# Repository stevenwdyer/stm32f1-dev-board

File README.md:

# stm32f1-dev-board

This board is an STM32F103-based development platform, designed for prototyping and developing embedded applications. The design includes:

* An STM32F103C8T6 microcontroller, which features an ARM Cortex-M3 core and 128kB of flash.

* Support for multiple communication protocols, including CANbus, LINbus, I<sup>2</sup>C, SPI, USB, and UART.

* Dual clock sources, featuring a 32.768kHz crystal for precise RTC functionality, as well as an 8MHz system clock.

* An SWD interface, enabling firmware flashing and in-circuit debugging using an external ST-LINK.

* A 5V to 3.3V linear regulator, providing power for the MCU and all onboard circuitry from the USB input.

* User interface, via a reset button and a power indicator LED.

* A standardized form factor, with a 19x50mm footprint and 2.54mm pitch headers, enabling compatibility with standard breadboards for rapid prototyping.

### Images ###

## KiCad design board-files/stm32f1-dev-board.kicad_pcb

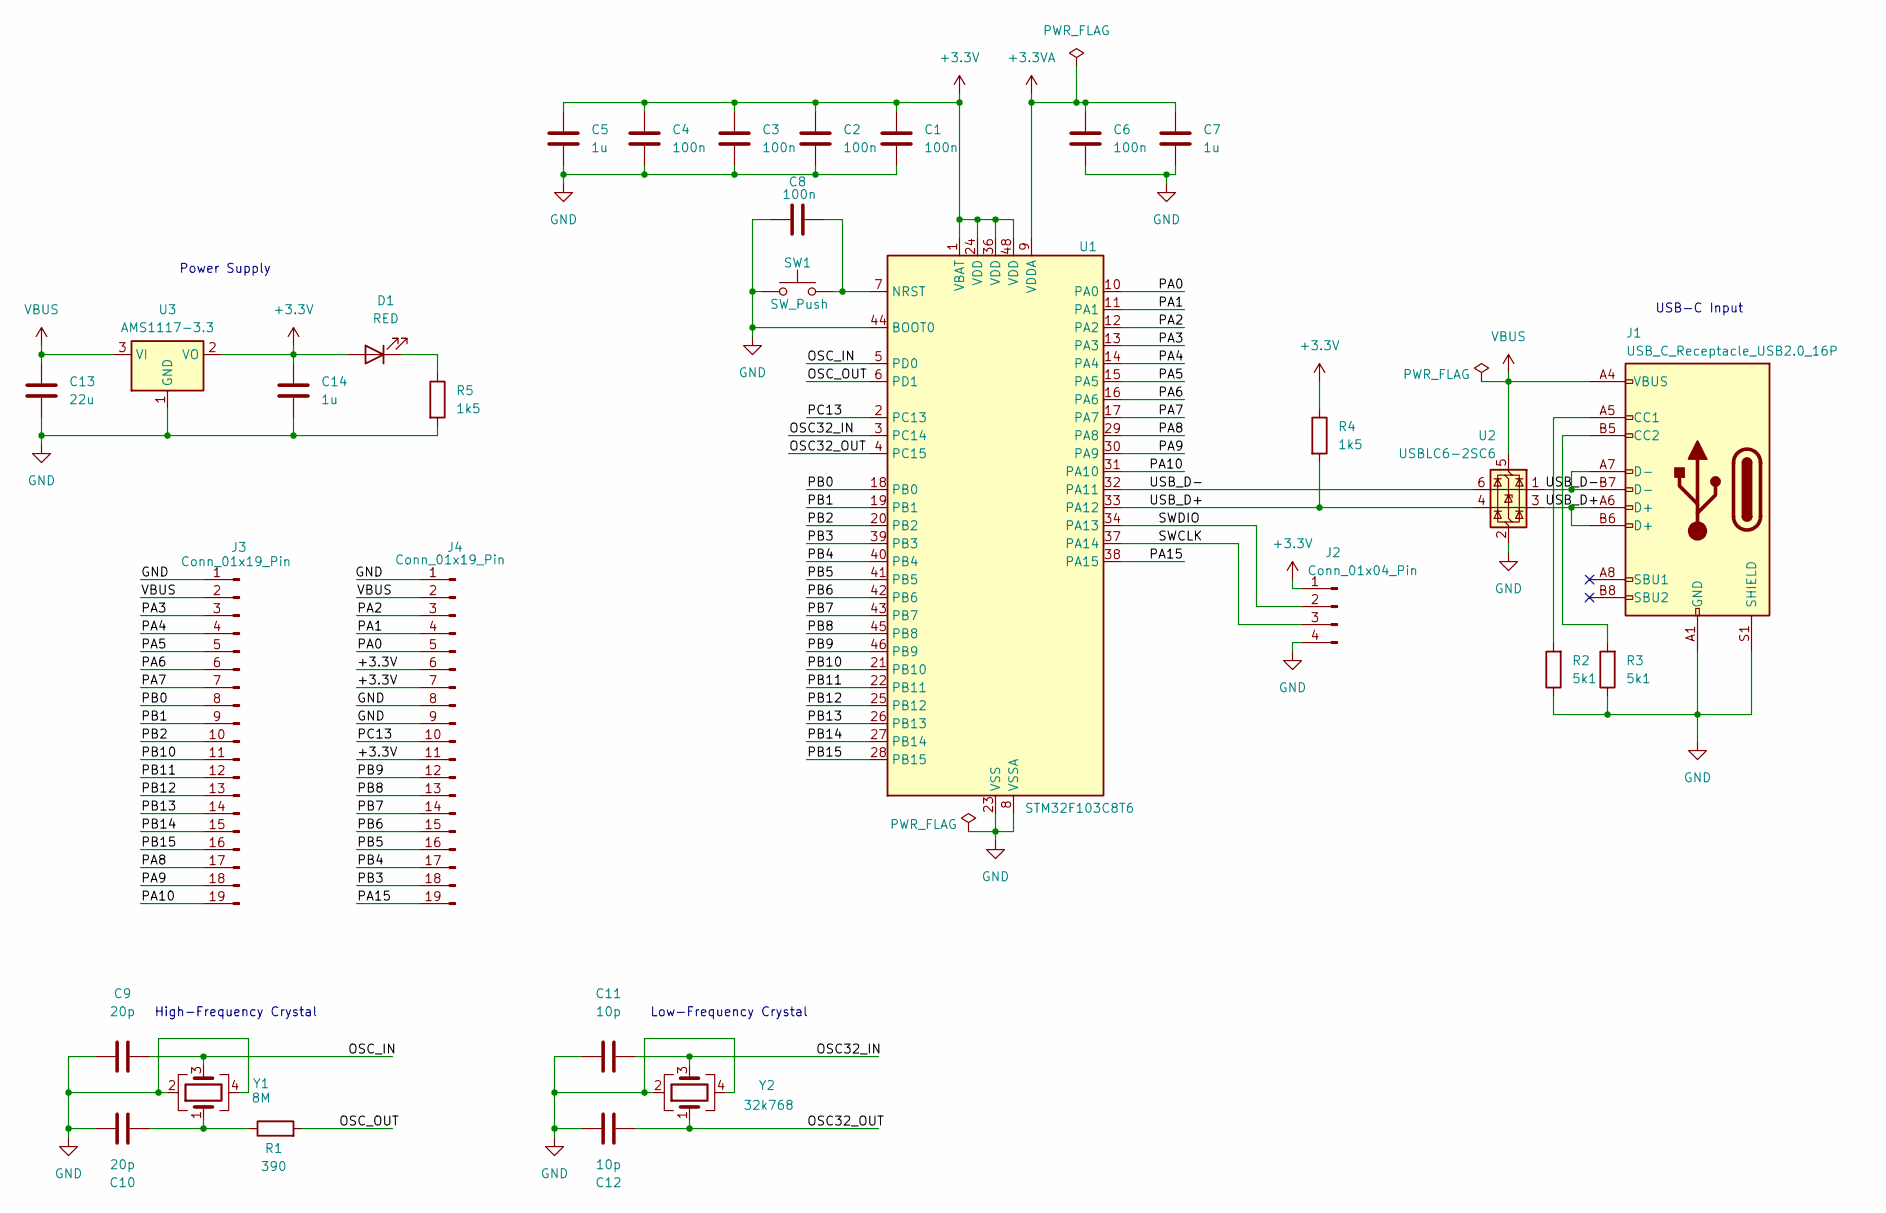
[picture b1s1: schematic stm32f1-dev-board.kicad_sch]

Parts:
C1, C2, C3, C4, C6, C8: 100n; C_0402_1005Metric
C5, C7, C14: 1u; C_0402_1005Metric
C9, C10: 20p; C_0402_1005Metric
C11, C12: 10p; C_0402_1005Metric
C13: 22u; C_0805_2012Metric
D1: RED; LED_0201_0603Metric
J1: USB_C_Receptacle_USB2.0_16P; USB_C_Receptacle_GCT_USB4105-xx-A_16P_TopMnt_Horizontal
J2: Conn_01x04_Pin; PinHeader_1x04_P2.54mm_Vertical
J3, J4: Conn_01x19_Pin; PinHeader_1x19_P2.54mm_Vertical
R1: 390; R_0402_1005Metric
R2, R3: 5k1; R_0402_1005Metric
R4, R5: 1k5; R_0402_1005Metric
SW1: SW_Push; SW_SPST_PTS810
U1: STM32F103C8T6; LQFP-48_7x7mm_P0.5mm
U2: USBLC6-2SC6; SOT-23-6
U3: AMS1117-3.3; SOT-223-3_TabPin2
Y1: 8M; Crystal_SMD_3225-4Pin_3.2x2.5mm
Y2: 32k768; Crystal_SMD_3225-4Pin_3.2x2.5mm

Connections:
+3.3V: C1.1, C2.1, C3.1, C4.1, C5.1, C14.1, D1.2 (A), J2.1, J4.6, J4.7, J4.11, R4.1, U1.1 (VBAT), U1.24 (VDD), U1.36 (VDD), U1.48 (VDD), U3.2 (VO)
+3.3VA: C6.1, C7.1, U1.9 (VDDA)
/OSC32_IN: C11.2, U1.3 (PC14), Y2.3
/OSC32_OUT: C12.2, U1.4 (PC15), Y2.1
/OSC_IN: C9.2, U1.5 (PD0), Y1.3
/OSC_OUT: R1.2, U1.6 (PD1)
/PA0: J4.5, U1.10 (PA0)
/PA1: J4.4, U1.11 (PA1)
/PA2: J4.3, U1.12 (PA2)
/PA3: J3.3, U1.13 (PA3)
/PA4: J3.4, U1.14 (PA4)
/PA5: J3.5, U1.15 (PA5)
/PA6: J3.6, U1.16 (PA6)
/PA7: J3.7, U1.17 (PA7)
/PA8: J3.17, U1.29 (PA8)
/PA9: J3.18, U1.30 (PA9)
/PA10: J3.19, U1.31 (PA10)
/PA15: J4.19, U1.38 (PA15)
/PB0: J3.8, U1.18 (PB0)
/PB1: J3.9, U1.19 (PB1)
/PB2: J3.10, U1.20 (PB2)
/PB3: J4.18, U1.39 (PB3)
/PB4: J4.17, U1.40 (PB4)
/PB5: J4.16, U1.41 (PB5)
/PB6: J4.15, U1.42 (PB6)
/PB7: J4.14, U1.43 (PB7)
/PB8: J4.13, U1.45 (PB8)
/PB9: J4.12, U1.46 (PB9)
/PB10: J3.11, U1.21 (PB10)
/PB11: J3.12, U1.22 (PB11)
/PB12: J3.13, U1.25 (PB12)
/PB13: J3.14, U1.26 (PB13)
/PB14: J3.15, U1.27 (PB14)
/PB15: J3.16, U1.28 (PB15)
/PC13: J4.10, U1.2 (PC13)
/SWCLK: J2.3, U1.37 (PA14)
/SWDIO: J2.2, U1.34 (PA13)
/USB_D+: J1.A6 (D+), J1.B6 (D+), R4.2, U1.33 (PA12), U2.3 (I/O2), U2.4 (I/O2)
/USB_D-: J1.A7 (D-), J1.B7 (D-), U1.32 (PA11), U2.1 (I/O1), U2.6 (I/O1)
GND: C1.2, C2.2, C3.2, C4.2, C5.2, C6.2, C7.2, C8.1, C9.1, C10.1, C11.1, C12.1, C13.2, C14.2, J1.A1 (GND), J1.A12 (GND), J1.B1 (GND), J1.B12 (GND), J1.S1 (SHIELD), J2.4, J3.1, J4.1, J4.8, J4.9, R2.1, R3.1, R5.2, SW1.1, U1.8 (VSSA), U1.23 (VSS), U1.35 (VSS), U1.44 (BOOT0), U1.47 (VSS), U2.2 (GND), U3.1 (GND), Y1.2, Y1.4, Y2.2, Y2.4
unnamed: C10.2, R1.1, Y1.1
unnamed: D1.1 (K), R5.1
unnamed: J1.A5 (CC1), R2.2
unnamed: J1.B5 (CC2), R3.2
unnamed: C8.2, SW1.2, U1.7 (NRST)
VBUS: C13.1, J1.A4 (VBUS), J1.A9 (VBUS), J1.B4 (VBUS), J1.B9 (VBUS), J3.2, J4.2, U2.5 (VBUS), U3.3 (VI)

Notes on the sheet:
USB-C Input
Power Supply
High-Frequency Crystal
Low-Frequency Crystal

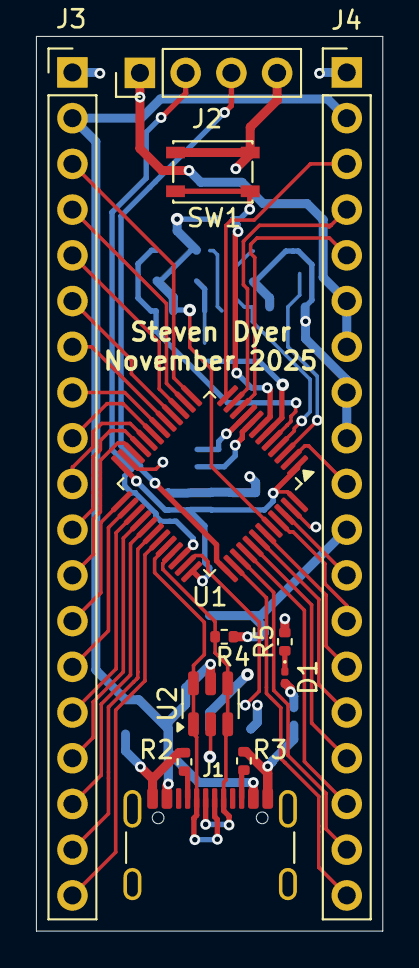
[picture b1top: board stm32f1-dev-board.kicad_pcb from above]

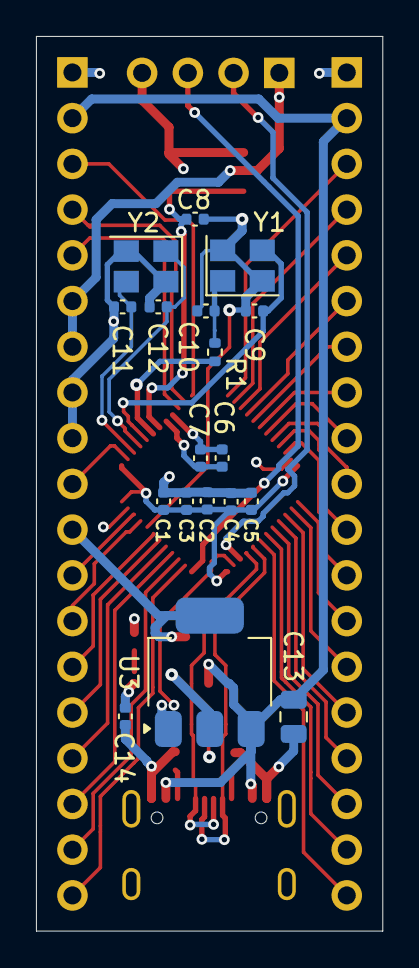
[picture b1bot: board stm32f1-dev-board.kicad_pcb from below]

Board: 4 copper layers, 19.2 x 49.7 mm, 30 parts (18 on the bottom side), 46 nets.

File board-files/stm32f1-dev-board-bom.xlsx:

Comment | Designator | Footprint | JLCPCB Part #（optional）
100n | C1,C2,C3,C4,C6,C8 | Capacitor_SMD:C_0402_1005Metric | https://mm.digikey.com/Volume0/opasdata/d220001/medias/docus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
1u | C5,C7,C14 | Capacitor_SMD:C_0402_1005Metric | https://mm.digikey.com/Volume0/opasdata/d220001/medias/docus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
20p | C9,C10 | Capacitor_SMD:C_0402_1005Metric | https://search.murata.co.jp/Ceramy/image/img/A01X/G101/ENG/G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
10p | C11,C12 | Capacitor_SMD:C_0402_1005Metric | https://mm.digikey.com/Volume0/opasdata/d220001/medias/docus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
22u | C13 | Capacitor_SMD:C_0805_2012Metric | https://mm.digikey.com/Volume0/opasdata/d220001/medias/docus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
RED | D1 | LED_SMD:LED_0201_0603Metric | https://www.we-online.com/components/products/datasheet/1540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
USB_C_Receptacle_USB2.0_16P | J1 | Connector_USB:USB_C_Receptacle_GCT_USB4105-xx-A_16P_TopMnt_Horizontal | https://www.usb.org/sites/default/files/documents/usb_type-c.zip
Conn_01x04_Pin | J2 | Connector_PinHeader_2.54mm:PinHeader_1x04_P2.54mm_Vertical | https://www.we-online.com/components/products/datasheet/6130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
Conn_01x19_Pin | J3,J4 | Connector_PinHeader_2.54mm:PinHeader_1x19_P2.54mm_Vertical | https://app.adam-tech.com/products/download/data_sheet/20160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
390 | R1 | Resistor_SMD:R_0402_1005Metric | https://www.yageo.com/upload/media/product/products/datashee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
5k1 | R2,R3 | Resistor_SMD:R_0402_1005Metric | https://www.digikey.ca/en/products/detail/yageo/RC0402FR-075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
1k5 | R4,R5 | Resistor_SMD:R_0402_1005Metric | https://www.yageo.com/upload/media/product/products/datashee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
SW_Push | SW1 | Button_Switch_SMD:SW_SPST_PTS810 | https://www.ckswitches.com/media/1476/pts810.pdf
STM32F103C8T6 | U1 | Package_QFP:LQFP-48_7x7mm_P0.5mm | https://www.st.com/resource/en/datasheet/stm32f103c8.pdf
USBLC6-2SC6 | U2 | Package_TO_SOT_SMD:SOT-23-6 | https://www.st.com/resource/en/datasheet/usblc6-2.pdf
AMS1117-3.3 | U3 | Package_TO_SOT_SMD:SOT-223-3_TabPin2 | http://www.advanced-monolithic.com/pdf/ds1117.pdf
8M | Y1 | Crystal:Crystal_SMD_3215-2Pin_3.2x2.5mm | https://www.waldom.com/upload/parts/datasheets/mf-abr/abr-as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
32k768 | Y2 | Crystal:Crystal_SMD_2012-2Pin_3.2x2.5mm | https://abracon.com/Resonators/ABS06.pdf

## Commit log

2025-11-15 Add board files
2025-11-15 Update gerber files
